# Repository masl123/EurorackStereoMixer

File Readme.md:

## Eurorack Stereo Mixer

This Eurorack module allows to mix stereo signals from up to 4 channels into one while also allowing to 
change the volume for each of the channels. The master volume can also be changed.
By plugging a mono signal into the left input of a channel, the signal is mirrored to the right 
channel of the mixer. This allows for mixing mono and stereo signals.

The module consists of 2 PCBs and a Frontpanel.

Based on a design from [circuitbasics](https://www.circuitbasics.com/what-are-audio-mixers/).

**Note**: The current release 1.0 is untested. I did test version 0.1 however
and it does work fine. Only some smaller adjustments were made in comparison to the version I built.

### Releases
Check the release folder for the different releases of this module and the corresponding BOMs.
Included gerber files should work for JLC-PCB. 

### Images

|                                   |                                   | 
|-----------------------------------|-----------------------------------|
|   |   |
|    |    |
|    |                                   |

### Changelog
Version 0.1:
 - initial design done

Version 1.0:
 - initial public release
 - placement of one potentiometer was slightly off.
 - adjusted text on PCBs slightly to include the repository name and license information

### License
Licensed under the TAPR Open Hardware License (www.tapr.org/OHL)

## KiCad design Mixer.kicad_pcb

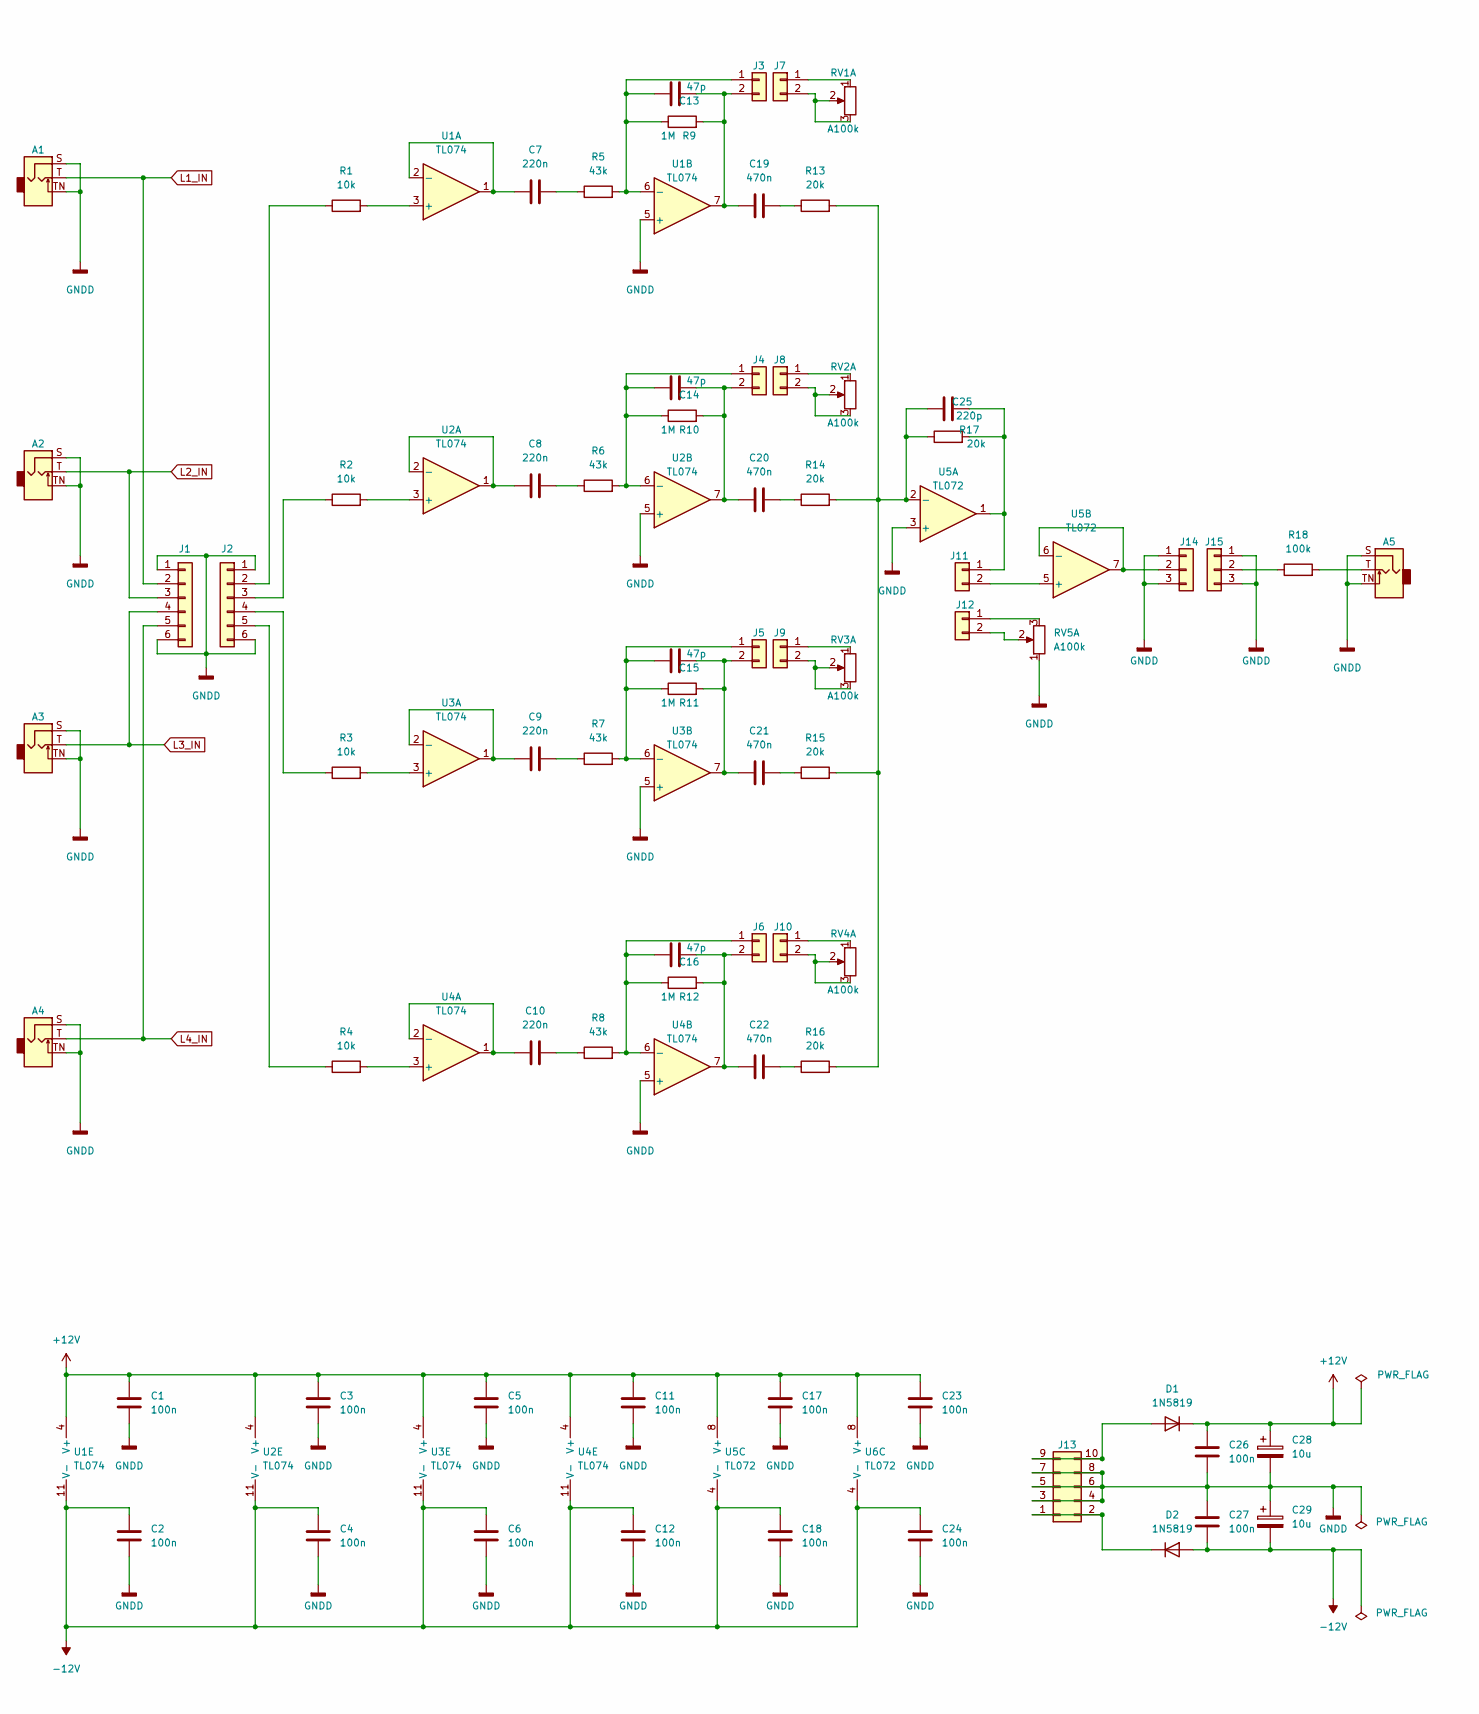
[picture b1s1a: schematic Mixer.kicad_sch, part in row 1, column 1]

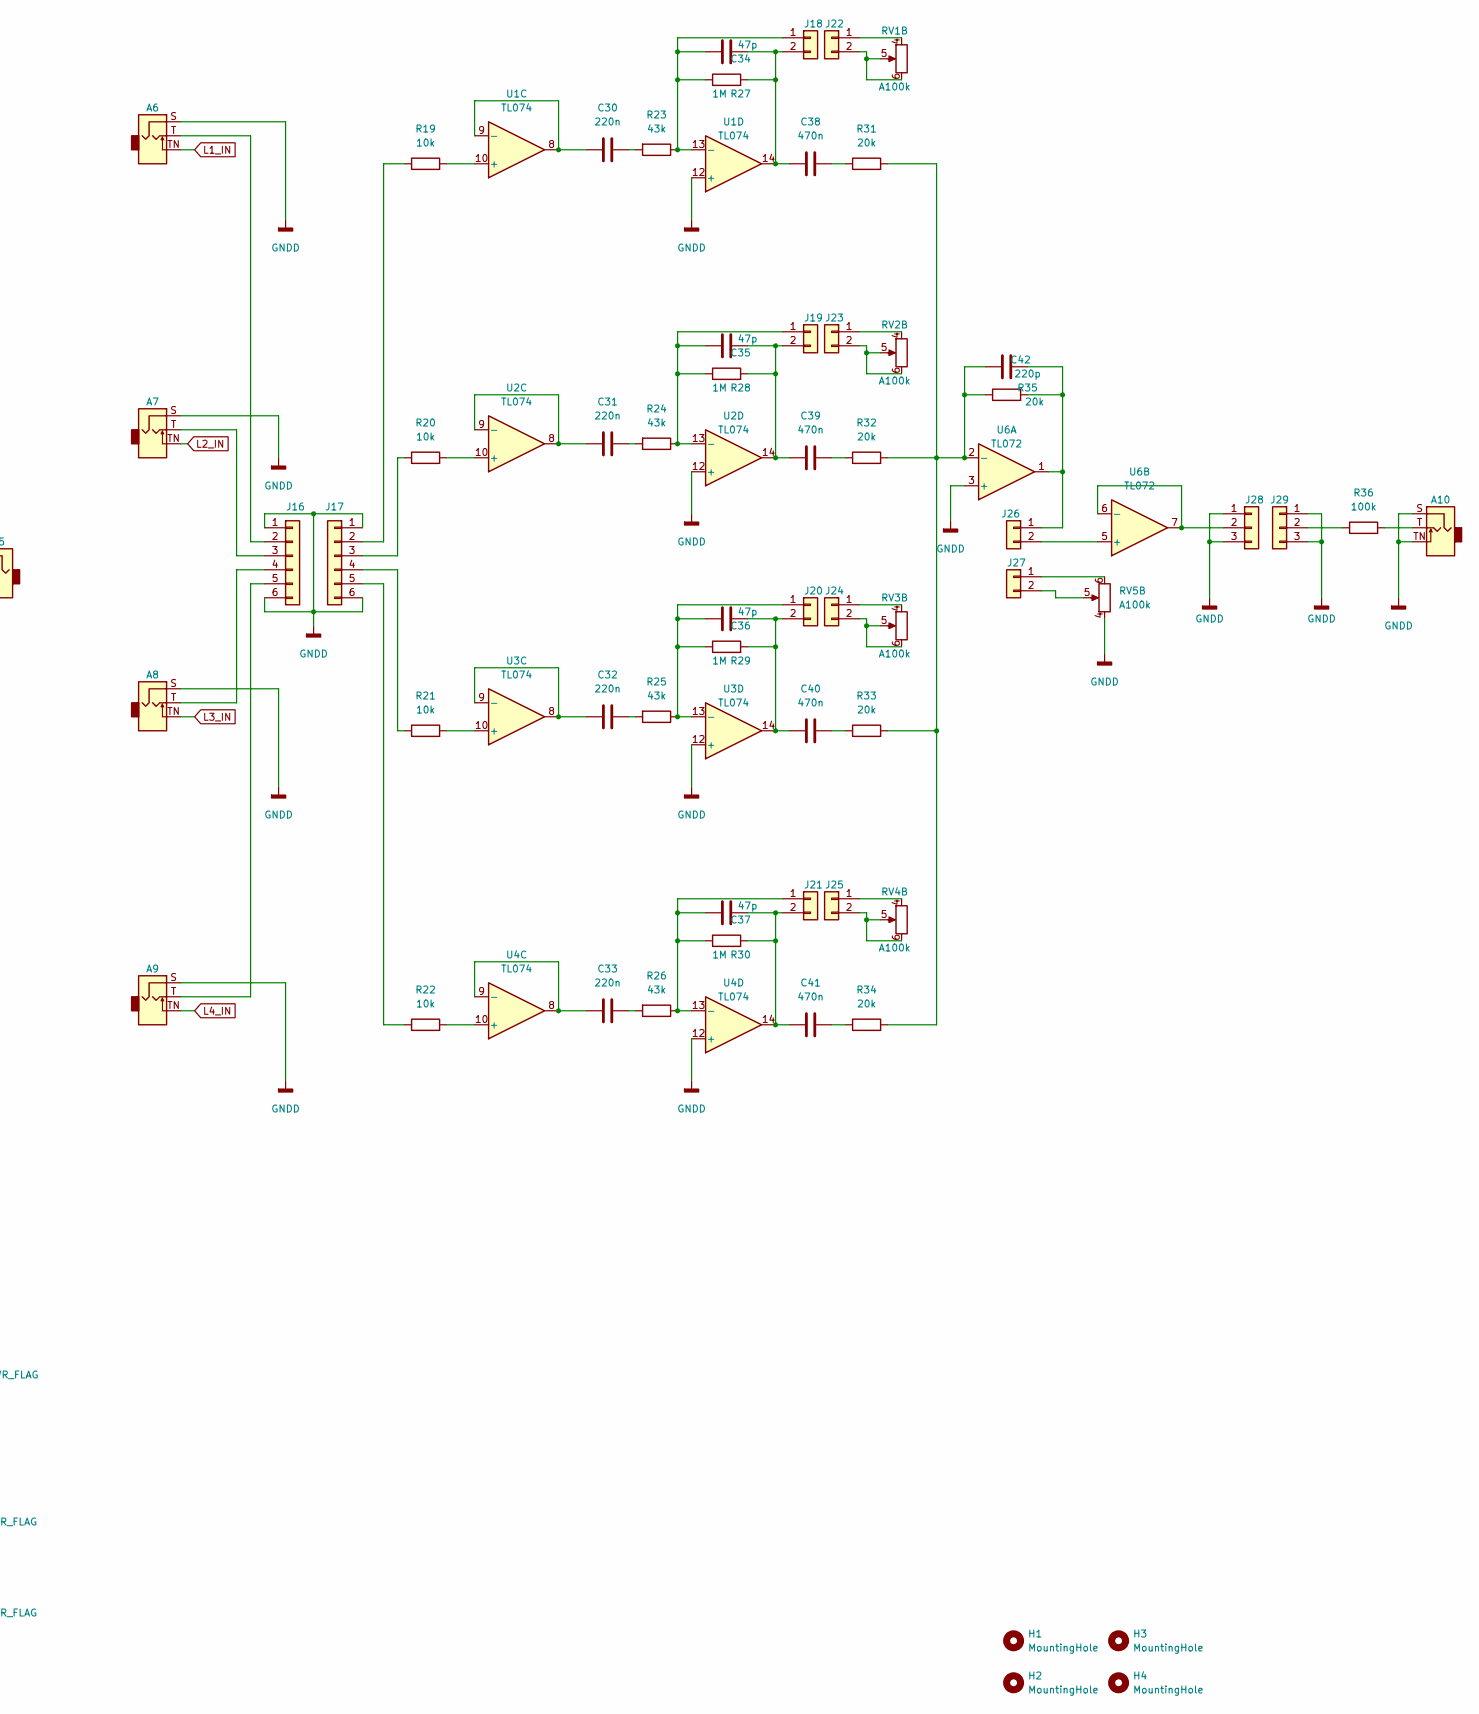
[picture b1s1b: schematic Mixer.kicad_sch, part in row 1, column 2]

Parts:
A1, A2, A3, A4, A5, A6, A7, A8, A9, A10: Jack_3.5mm_QingPu_WQP-PJ398SM_Vertical
C1, C2, C3, C4, C5, C6, C11, C12, C17, C18, C23, C24, C26, C27: 100n; C_0805_2012Metric_Pad1.18x1.45mm_HandSolder; Part CC0805KPX7R9104
C7, C8, C9, C10, C30, C31, C32, C33: 220n; C_Rect_L7.2mm_W2.5mm_P5.00mm_FKS2_FKP2_MKS2_MKP2; Part B32529C0224J000
C13, C14, C15, C16, C34, C35, C36, C37: 47p; C_Disc_D4.3mm_W1.9mm_P5.00mm; Part CT40805N470J500F3R
C19, C20, C21, C22, C38, C39, C40, C41: 470n; C_Rect_L7.2mm_W3.5mm_P5.00mm_FKS2_FKP2_MKS2_MKP2; Part B32529C0474J289
C25, C42: 220p; C_Disc_D4.3mm_W1.9mm_P5.00mm; Part CT40805N221J500F3R
C28, C29: 10u; CP_Radial_D5.0mm_P2.00mm; Part EEUEB1A101S
D1, D2: 1N5819; D_DO-41_SOD81_P10.16mm_Horizontal
H1, H2, H3, H4: MountingHole; MountingHole_3.2mm_M3
J1, J16: Conn_01x06; PinSocket_1x06_P2.54mm_Vertical
J2, J17: Conn_01x06; PinHeader_1x06_P2.54mm_Vertical
J3, J4, J5, J6, J11, J18, J19, J20, J21, J26: Conn_01x02; PinHeader_1x02_P2.54mm_Vertical
J7, J8, J9, J10, J12, J22, J23, J24, J25, J27: Conn_01x02; PinSocket_1x02_P2.54mm_Vertical
J13: PinHeader_2x05_P2.54mm_Vertical
J14, J28: Conn_01x03; PinHeader_1x03_P2.54mm_Vertical
J15, J29: Conn_01x03; PinSocket_1x03_P2.54mm_Vertical
R1, R2, R3, R4, R19, R20, R21, R22: 10k; R_Axial_DIN0207_L6.3mm_D2.5mm_P2.54mm_Vertical
R5, R6, R7, R8, R23, R24, R25, R26: 43k; R_Axial_DIN0207_L6.3mm_D2.5mm_P2.54mm_Vertical
R9, R10, R11, R12, R27, R28, R29, R30: 1M; R_Axial_DIN0207_L6.3mm_D2.5mm_P2.54mm_Vertical
R13, R14, R15, R16, R17, R31, R32, R33, R34, R35: 20k; R_Axial_DIN0207_L6.3mm_D2.5mm_P2.54mm_Vertical
R18, R36: 100k; R_Axial_DIN0207_L6.3mm_D2.5mm_P10.16mm_Horizontal
RV1, RV2, RV3, RV4, RV5: A100k; Potentiometer_Alpha_RD902F-40-00D_Dual_Vertical
U1, U2, U3, U4: TL074; DIP-14_W7.62mm_Socket_LongPads
U5, U6: TL072; DIP-8_W7.62mm_Socket_LongPads

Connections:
+12V: C1.1, C3.1, C5.1, C11.1, C17.1, C23.1, C26.1, C28.1, D1.1 (K), U1.4 (V+), U2.4 (V+), U3.4 (V+), U4.4 (V+), U5.8 (V+), U6.8 (V+)
-12V: C2.1, C4.2, C6.2, C12.2, C18.2, C24.2, C27.2, C29.2, D2.2 (A), U1.11 (V-), U2.11 (V-), U3.11 (V-), U4.11 (V-), U5.4 (V-), U6.4 (V-)
GNDD: A1.S, A1.TN, A2.S, A2.TN, A3.S, A3.TN, A4.S, A4.TN, A5.S, A5.TN, A6.S, A7.S, A8.S, A9.S, A10.S, A10.TN, C1.2, C2.2, C3.2, C4.1, C5.2, C6.1, C11.2, C12.1, C17.2, C18.1, C23.2, C24.1, C26.2, C27.1, C28.2, C29.1, J1.1, J1.6, J2.1, J2.6, J13.3, J13.4, J13.5, J13.6, J13.7, J13.8, J14.1, J14.3, J15.1, J15.3, J16.1, J16.6, J17.1, J17.6, J28.1, J28.3, J29.1, J29.3, RV5.1, RV5.4, U1.5 (+), U1.12 (+), U2.5 (+), U2.12 (+), U3.5 (+), U3.12 (+), U4.5 (+), U4.12 (+), U5.3 (+), U6.3 (+)
L1_IN: A1.T, A6.TN, J1.2
L2_IN: A2.T, A7.TN, J1.3
L3_IN: A3.T, A8.TN, J1.4
L4_IN: A4.T, A9.TN, J1.5
unnamed: A5.T, R18.2
unnamed: A6.T, J16.2
unnamed: A7.T, J16.3
unnamed: A8.T, J16.4
unnamed: A9.T, J16.5
unnamed: A10.T, R36.2
unnamed: C7.1, R5.1
unnamed: C7.2, U1.1, U1.2 (-)
unnamed: C8.1, R6.1
unnamed: C8.2, U2.1, U2.2 (-)
unnamed: C9.1, R7.1
unnamed: C9.2, U3.1, U3.2 (-)
unnamed: C10.1, R8.1
unnamed: C10.2, U4.1, U4.2 (-)
unnamed: C13.1, J3.1, R5.2, R9.1, U1.6 (-)
unnamed: C13.2, C19.1, J3.2, R9.2, U1.7
unnamed: C14.1, J4.1, R6.2, R10.1, U2.6 (-)
unnamed: C14.2, C20.1, J4.2, R10.2, U2.7
unnamed: C15.1, J5.1, R7.2, R11.1, U3.6 (-)
unnamed: C15.2, C21.1, J5.2, R11.2, U3.7
unnamed: C16.1, J6.1, R8.2, R12.1, U4.6 (-)
unnamed: C16.2, C22.1, J6.2, R12.2, U4.7
unnamed: C19.2, R13.1
unnamed: C20.2, R14.1
unnamed: C21.2, R15.1
unnamed: C22.2, R16.1
unnamed: C25.1, R13.2, R14.2, R15.2, R16.2, R17.1, U5.2 (-)
unnamed: C25.2, J11.1, R17.2, U5.1
unnamed: C30.1, U1.8, U1.9 (-)
unnamed: C30.2, R23.2
unnamed: C31.1, U2.8, U2.9 (-)
unnamed: C31.2, R24.2
unnamed: C32.1, U3.8, U3.9 (-)
unnamed: C32.2, R25.2
unnamed: C33.1, U4.8, U4.9 (-)
unnamed: C33.2, R26.2
unnamed: C34.1, J18.1, R23.1, R27.1, U1.13 (-)
unnamed: C34.2, C38.1, J18.2, R27.2, U1.14
unnamed: C35.1, J19.1, R24.1, R28.1, U2.13 (-)
unnamed: C35.2, C39.1, J19.2, R28.2, U2.14
unnamed: C36.1, J20.1, R25.1, R29.1, U3.13 (-)
unnamed: C36.2, C40.1, J20.2, R29.2, U3.14
unnamed: C37.1, J21.1, R26.1, R30.1, U4.13 (-)
unnamed: C37.2, C41.1, J21.2, R30.2, U4.14
unnamed: C38.2, R31.1
unnamed: C39.2, R32.1
unnamed: C40.2, R33.1
unnamed: C41.2, R34.1
unnamed: C42.1, R31.2, R32.2, R33.2, R34.2, R35.1, U6.2 (-)
unnamed: C42.2, J26.1, R35.2, U6.1
unnamed: D1.2 (A), J13.9, J13.10
unnamed: D2.1 (K), J13.1, J13.2
unnamed: J2.2, R1.1
unnamed: J2.3, R2.1
unnamed: J2.4, R3.1
unnamed: J2.5, R4.1
unnamed: J7.1, RV1.1
unnamed: J7.2, RV1.2, RV1.3
unnamed: J8.1, RV2.1
unnamed: J8.2, RV2.2, RV2.3
unnamed: J9.1, RV3.1
unnamed: J9.2, RV3.2, RV3.3
unnamed: J10.1, RV4.1
unnamed: J10.2, RV4.2, RV4.3
unnamed: J11.2, U5.5 (+)
unnamed: J12.1, RV5.3
unnamed: J12.2, RV5.2
unnamed: J14.2, U5.6 (-), U5.7
unnamed: J15.2, R18.1
unnamed: J17.2, R19.1
unnamed: J17.3, R20.1
unnamed: J17.4, R21.1
unnamed: J17.5, R22.1
unnamed: J22.1, RV1.4
unnamed: J22.2, RV1.5, RV1.6
unnamed: J23.1, RV2.4
unnamed: J23.2, RV2.5, RV2.6
unnamed: J24.1, RV3.4
unnamed: J24.2, RV3.5, RV3.6
unnamed: J25.1, RV4.4
unnamed: J25.2, RV4.5, RV4.6
unnamed: J26.2, U6.5 (+)
unnamed: J27.1, RV5.6
unnamed: J27.2, RV5.5
unnamed: J28.2, U6.6 (-), U6.7
unnamed: J29.2, R36.1
unnamed: R1.2, U1.3 (+)
unnamed: R2.2, U2.3 (+)
unnamed: R3.2, U3.3 (+)
unnamed: R4.2, U4.3 (+)
unnamed: R19.2, U1.10 (+)
unnamed: R20.2, U2.10 (+)
unnamed: R21.2, U3.10 (+)
unnamed: R22.2, U4.10 (+)

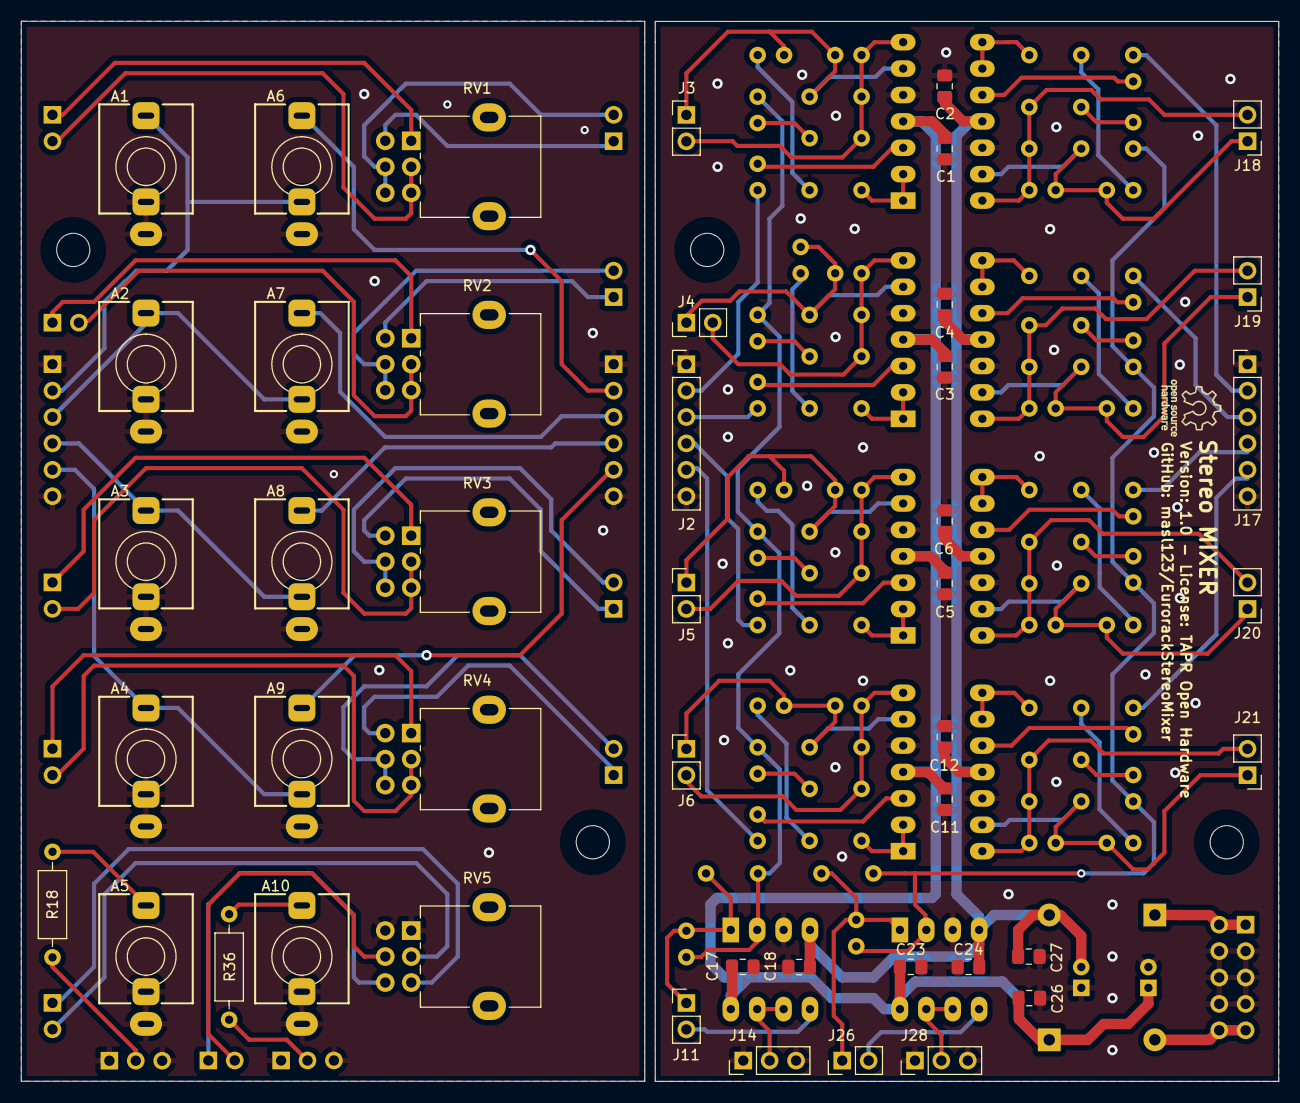
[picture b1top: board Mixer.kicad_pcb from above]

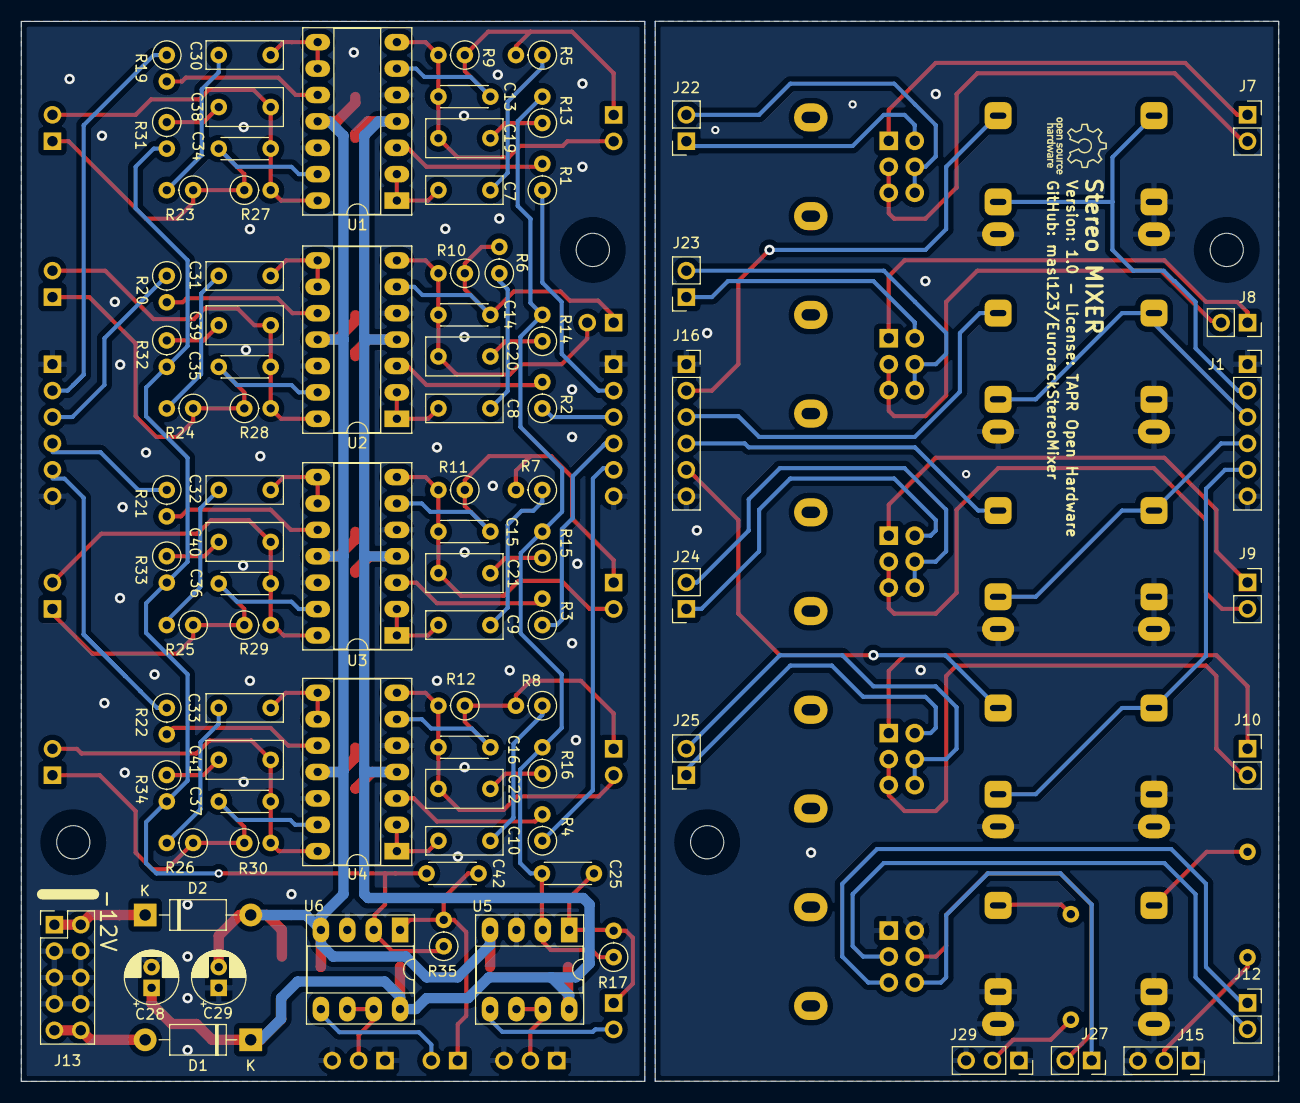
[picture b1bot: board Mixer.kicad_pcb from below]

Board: 2 copper layers, 121.0 x 102.0 mm, 134 parts (85 on the bottom side), 101 nets.

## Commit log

2023-11-12 Initial Release.

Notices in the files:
Mixer.kicad_pcb:
Version: 1.0 - License: TAPR Open Hardware
